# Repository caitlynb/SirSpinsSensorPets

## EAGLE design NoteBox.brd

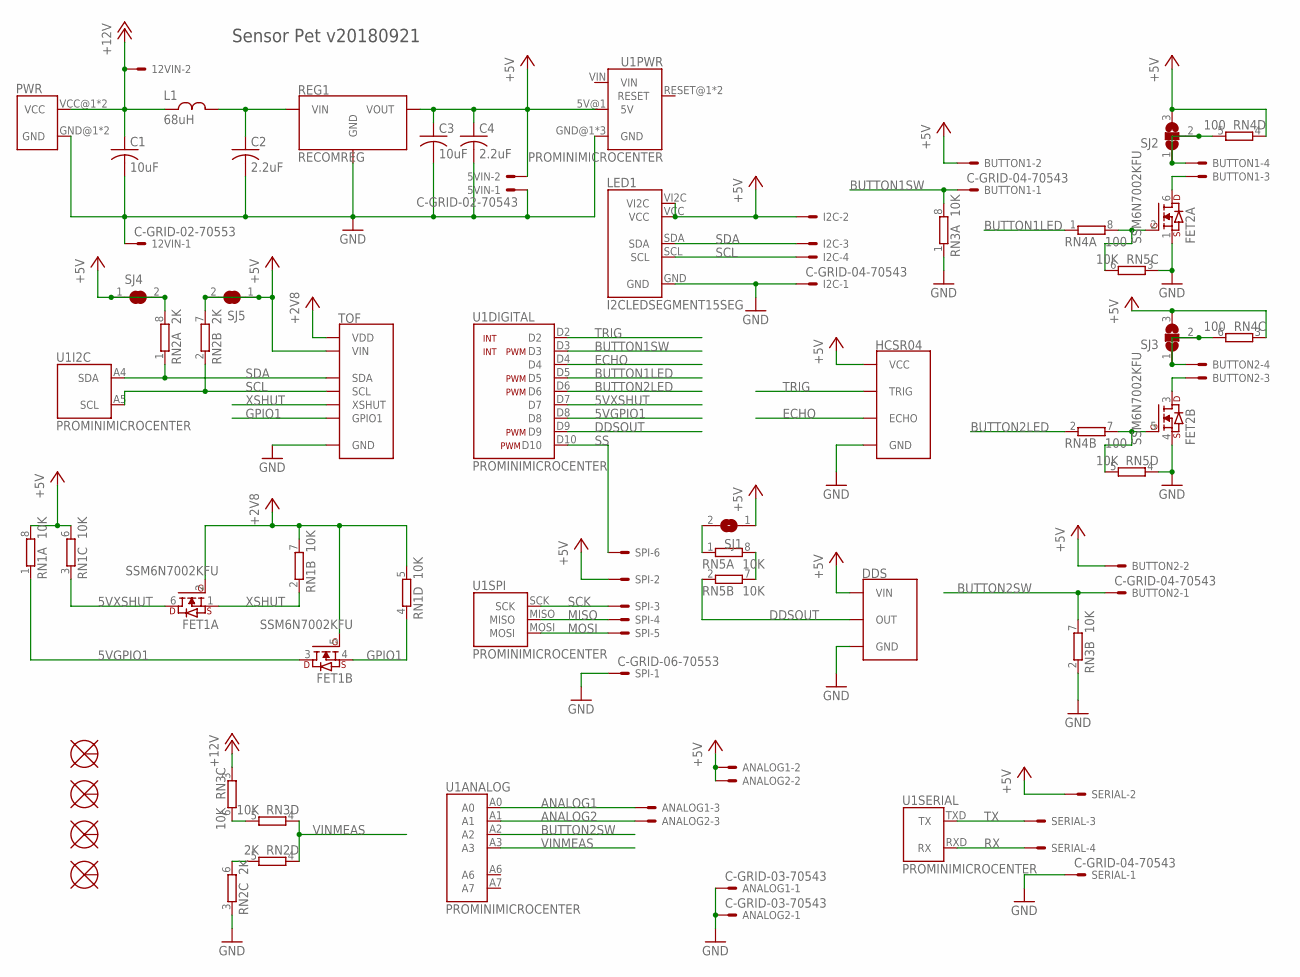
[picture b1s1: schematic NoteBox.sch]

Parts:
5VIN: C-GRID-02-70543; 70543-02
12VIN: C-GRID-02-70553; 70553-02
ANALOG1, ANALOG2: C-GRID-03-70543; 70543-03
BUTTON1, BUTTON2: C-GRID-04-70543; 70543-04
C1, C3: 10uF; C1206K
C2, C4: 2.2uF; C0805K
DDS: POLOLUDDS
FET1, FET2: SSM6N7002KFU; US6
HCSR04: HCSR04
I2C: C-GRID-04-70543; 70543-04
L1: 68uH; 6060
LED1: I2CLEDSEGMENT15SEG; ADAFRUITI2CLEDSEGMENT
PWR: POWERPOLERA1X2; PP-RA-1X2
REG1: RECOMREG
RN1, RN3, RN5: 10K; CAY16
RN2: 2K; CAY16
RN4: 100; CAY16
SERIAL: C-GRID-04-70543; 70543-04
SJ1, SJ4, SJ5: SJ
SJ2, SJ3: SJ2W; SJ_2
SPI: C-GRID-06-70553; 70553-06
TOF: POLOLUTOF
U1: PROMINIMICROCENTER; MICROCENTER-ARDUINO-PROMINI
U$5, U$6, U$7, U$8: MOUNT6-32; 6-32

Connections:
5VGPIO1: FET1.3 (D), RN1.1, U1.D8
5VXSHUT: FET1.6 (D), RN1.3 (1), U1.D7
+2V8: FET1.2 (G), FET1.5 (G), RN1.5 (2), RN1.7 (2), TOF.VDD
+5V: 5VIN.2, ANALOG1.2, ANALOG2.2, BUTTON1.2, BUTTON2.2, C3.1, C4.1, DDS.VIN, HCSR04.VCC, I2C.2, LED1.VCC, LED1.VI2C, REG1.3VOUT (VOUT), RN1.6 (2), RN1.8 (2), RN2.7 (2), RN2.8 (2), RN4.3 (1), RN4.4 (1), SERIAL.2, SJ1.1, SJ2.3, SJ3.3, SJ4.1, SJ4.2, SJ5.1, SJ5.2, SPI.2, TOF.VIN, U1.5V@1 (5V)
+12V: 12VIN.2, C1.1, L1.P$1, PWR.VCC@1 (VCC), PWR.VCC@2 (VCC), RN3.3 (1)
ANALOG1: ANALOG1.3, U1.A0
ANALOG2: ANALOG2.3, U1.A1
B1L+: BUTTON1.4, RN4.5 (2), SJ2.1, SJ2.2
B1L-: BUTTON1.3, FET2.6 (D)
B2L+: BUTTON2.4, RN4.6 (2), SJ3.1, SJ3.2
B2L-: BUTTON2.3, FET2.3 (D)
BUTTON1LED: RN4.1, U1.D5
BUTTON1SW: BUTTON1.1, RN3.8 (2), U1.D3
BUTTON2LED: RN4.2 (1), U1.D6
BUTTON2SW: BUTTON2.1, RN3.7 (2), U1.A2
DDSOUT: DDS.OUT, RN5.2 (1), U1.D9
ECHO: HCSR04.ECHO, U1.D4
GND: 5VIN.1, 12VIN.1, ANALOG1.1, ANALOG2.1, C1.2, C2.2, C3.2, C4.2, DDS.GND, FET2.1 (S), FET2.4 (S), HCSR04.GND, I2C.1, LED1.GND, PWR.GND@1 (GND), PWR.GND@2 (GND), REG1.2GND (GND), RN2.3 (1), RN3.1, RN3.2 (1), RN5.3 (1), RN5.4 (1), SERIAL.1, SPI.1, TOF.GND, U1.GND@1 (GND), U1.GND@2 (GND), U1.GND@3 (GND)
GPIO1: FET1.4 (S), RN1.4 (1), TOF.GPIO (GPIO1)
MISO: SPI.4, U1.MISO
MOSI: SPI.5, U1.MOSI
unnamed: RN3.5 (2), RN3.6 (2)
unnamed: C2.1, L1.P$2, REG1.1VIN (VIN)
unnamed: RN2.5 (2), RN2.6 (2)
unnamed: FET2.2 (G), RN4.8 (2), RN5.6 (2)
unnamed: FET2.5 (G), RN4.7 (2), RN5.5 (2)
unnamed: RN5.1, SJ1.2
unnamed: RN5.7 (2), RN5.8 (2)
RX: SERIAL.4, U1.RXD (RX)
SCK: SPI.3, U1.SCK
SCL: I2C.4, LED1.SCL, RN2.2 (1), TOF.SCL, U1.A5 (SCL)
SDA: I2C.3, LED1.SDA, RN2.1, TOF.SDA, U1.A4 (SDA)
SS: SPI.6, U1.D10
TRIG: HCSR04.TRIG, U1.D2
TX: SERIAL.3, U1.TXD (TX)
VIN: U1.VIN
VINMEAS: RN2.4 (1), RN3.4 (1), U1.A3
XSHUT: FET1.1 (S), RN1.2 (1), TOF.XSHUT

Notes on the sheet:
Sensor Pet v20180921

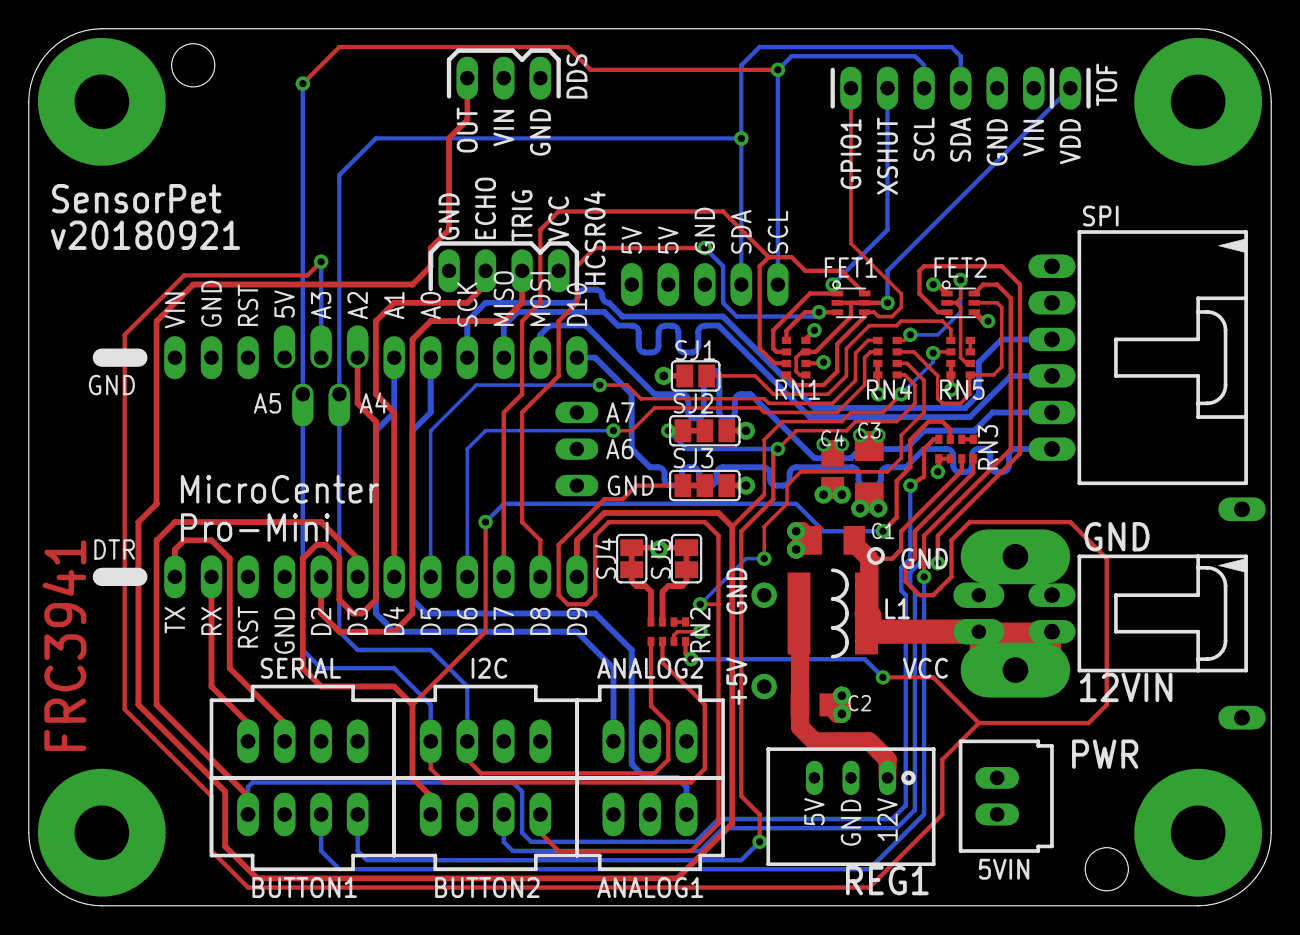
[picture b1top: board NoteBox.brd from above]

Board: 4 copper layers, 86.4 x 61.0 mm, 37 parts (0 on the bottom side), 37 nets.

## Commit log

2018-12-16 Initial Import from EdDay Pets
2018-12-16 initial trial with pets
2019-02-11 adding electronics information to repo
2019-02-12 basic change to make pets output binary data
